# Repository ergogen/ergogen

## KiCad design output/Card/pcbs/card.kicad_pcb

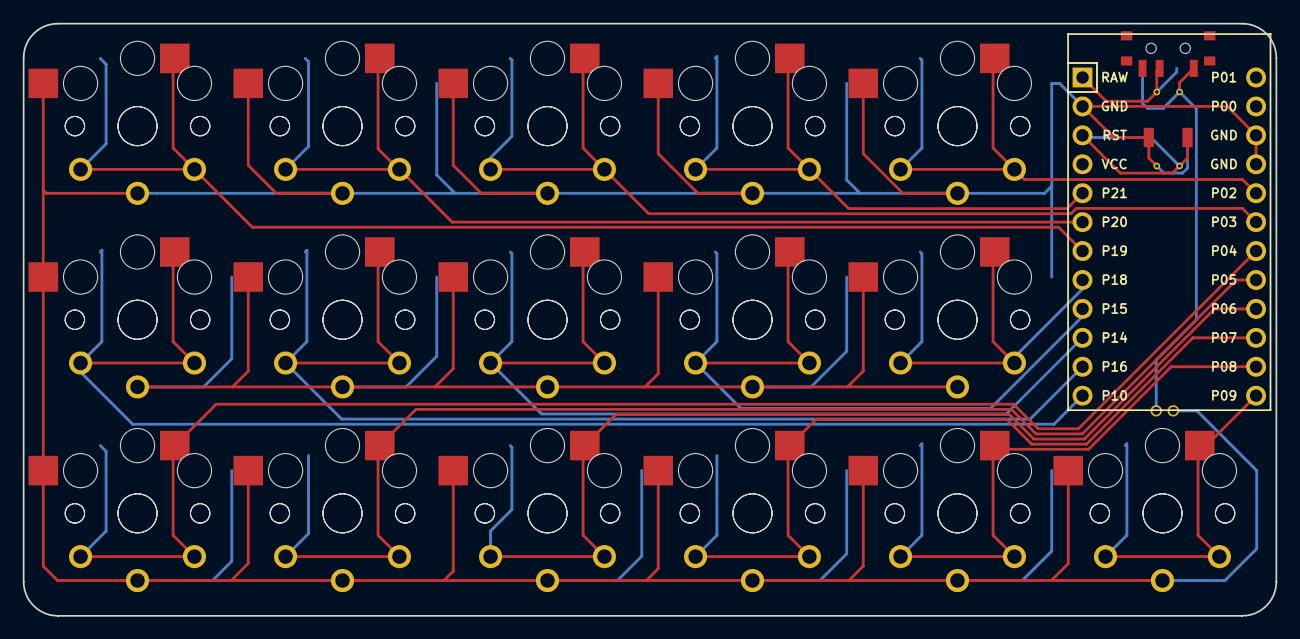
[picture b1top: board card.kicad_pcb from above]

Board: 2 copper layers, 110.0 x 52.0 mm, 33 parts (0 on the bottom side), 17 nets.

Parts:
MCU1: ProMicro
S1, S2, S3, S4, S5, S6, S7, S8, S9, S10, S11, S12, S13, S14, S15, S16, S17, S18, S19, S20, S21, S22, S23, S24, S25, S26, S27, S28, S29, S30, S31, S32: PG1350

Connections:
GND: MCU1.2, MCU1.15, MCU1.16, S1.2, S2.2, S3.2, S4.2, S5.2, S6.2, S7.2, S8.2, S9.2, S10.2, S11.2, S12.2, S13.2, S14.2, S15.2, S16.2, S17.2, S18.2, S19.2, S20.2, S21.2, S22.2, S23.2, S24.2, S25.2, S26.2, S27.2, S28.2, S29.2, S30.2, S31.2, S32.2
P2: MCU1.17, S29.1, S30.1
P3: MCU1.18, S17.1, S18.1
P4: MCU1.19, S1.1, S2.1
P5: MCU1.20, S7.1, S8.1
P6: MCU1.21, S13.1, S14.1
P7: MCU1.22, S19.1, S20.1
P8: MCU1.23, S25.1, S26.1
P9: MCU1.24, S31.1, S32.1
P10: MCU1.12, S3.1, S4.1
P14: MCU1.10, S15.1, S16.1
P15: MCU1.9, S21.1, S22.1
P16: MCU1.11, S9.1, S10.1
P18: MCU1.8, S27.1, S28.1
P19: MCU1.7, S5.1, S6.1
P20: MCU1.6, S11.1, S12.1
P21: MCU1.5, S23.1, S24.1

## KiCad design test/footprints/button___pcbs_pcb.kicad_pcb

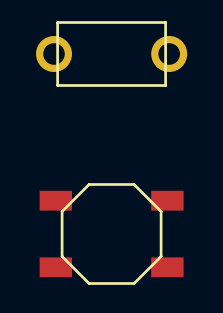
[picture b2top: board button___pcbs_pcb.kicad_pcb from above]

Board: 2 copper layers, 3 parts (0 on the bottom side), 2 nets, no tracks yet.

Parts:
B1, B2: SW_TACT_ALPS_SKQGABE010
B3: SW_TACT_PTS636_SK43_LFS

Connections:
from: B1.1, B2.1, B3.1
to: B1.2, B2.2, B3.2

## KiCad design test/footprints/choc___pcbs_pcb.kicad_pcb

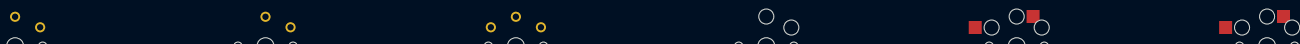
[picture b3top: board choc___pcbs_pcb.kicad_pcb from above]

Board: 2 copper layers, 6 parts (0 on the bottom side), 2 nets, no tracks yet.

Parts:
S1, S2, S3, S4, S5, S6: PG1350

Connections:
from: S1.1, S2.1, S3.1, S4.1, S5.1, S6.1
to: S1.2, S2.2, S3.2, S4.2, S5.2, S6.2

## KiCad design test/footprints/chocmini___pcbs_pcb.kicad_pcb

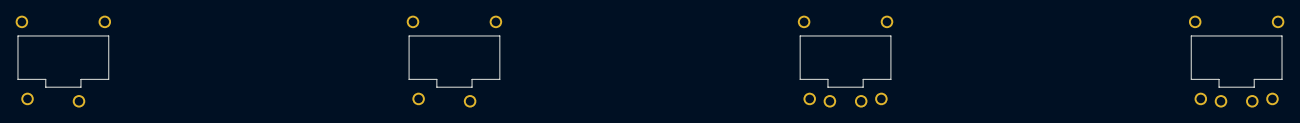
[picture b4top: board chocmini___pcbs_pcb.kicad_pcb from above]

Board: 2 copper layers, 4 parts (0 on the bottom side), 2 nets, no tracks yet.

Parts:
S1, S2, S3, S4: Kailh_PG1232

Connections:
from: S1.1, S2.1, S3.1, S4.1
to: S1.2, S2.2, S3.2, S4.2

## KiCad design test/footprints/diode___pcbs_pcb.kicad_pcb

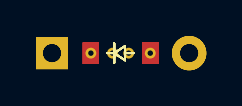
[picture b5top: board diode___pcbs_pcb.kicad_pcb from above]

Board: 2 copper layers, 5 parts (0 on the bottom side), 2 nets, no tracks yet.

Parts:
D1, D2, D3, D4, D5: ComboDiode

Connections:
from: D1.2, D2.2, D3.2, D4.2, D5.2
to: D1.1, D2.1, D3.1, D4.1, D5.1
